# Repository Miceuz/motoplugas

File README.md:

motoplugas
==========

A revolution counting jig for variable frequency drive driven pulley system

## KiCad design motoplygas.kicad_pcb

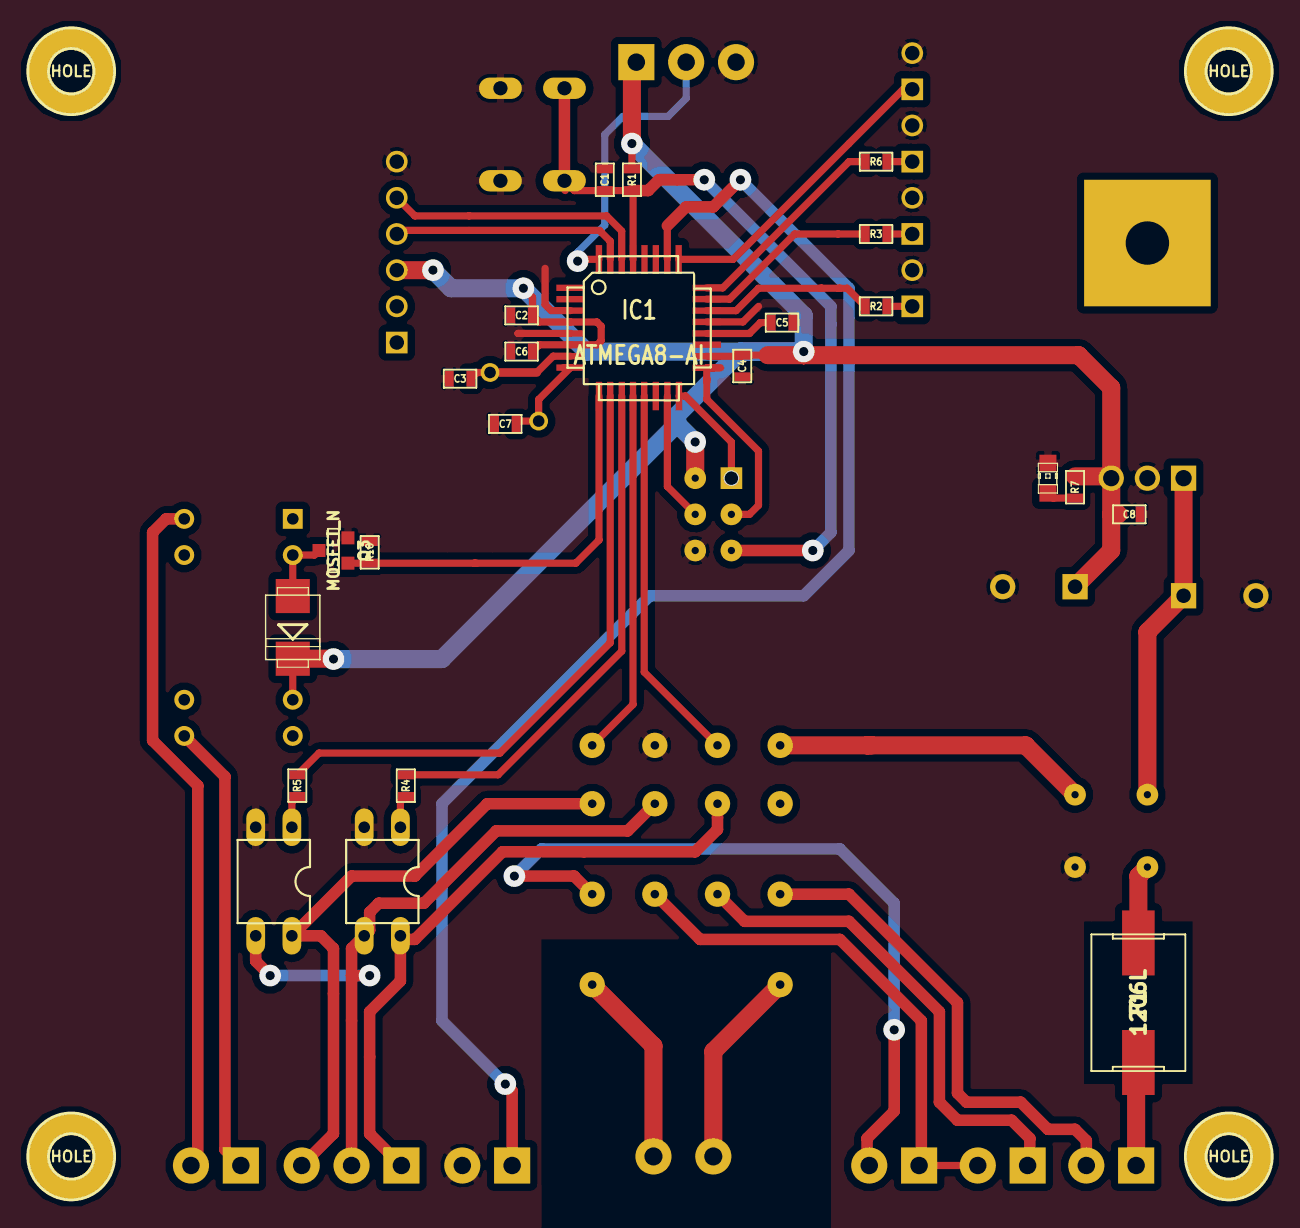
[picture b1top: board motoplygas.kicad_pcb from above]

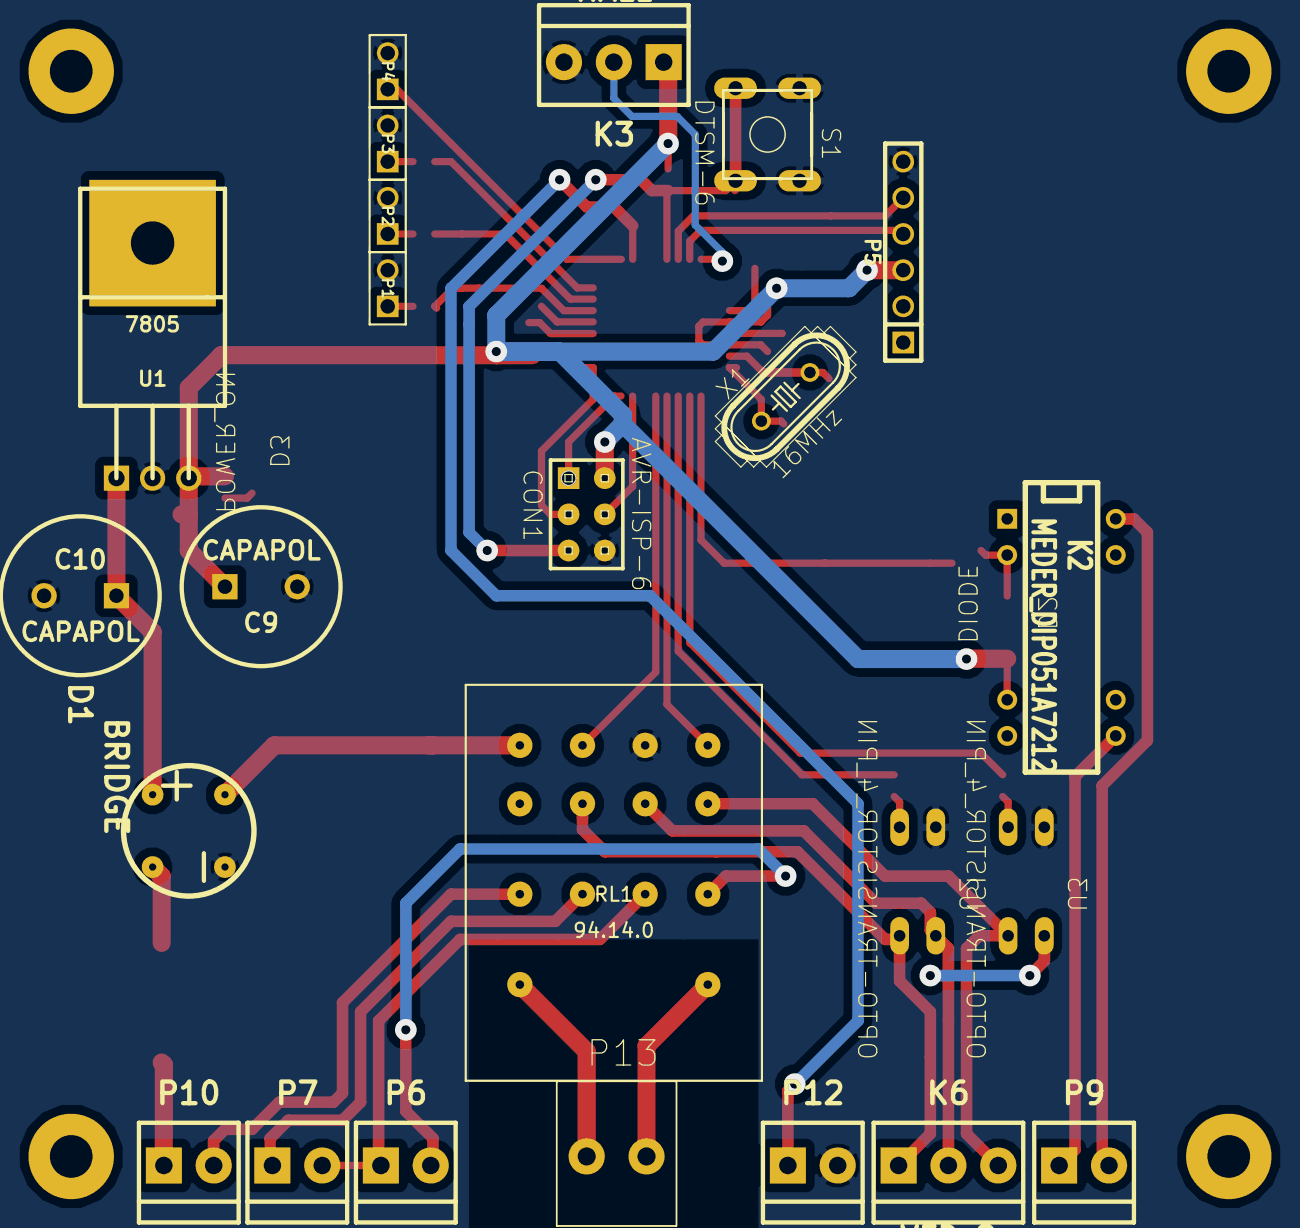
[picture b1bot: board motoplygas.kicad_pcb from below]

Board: 2 copper layers, 49 parts (22 on the bottom side), 44 nets.

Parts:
C1, C2, C4, C5, C6, C8: C; SM0603_Capa
C3, C7: 18pF; SM0603_Capa
C9, C10: CAPAPOL; C2V10
CON1: AVR-ISP-6; atmel-AVR-ISP-6
D1: BRIDGE; Bridge-rond
D2: DIODE; diode-SMB
D3: POWER_ON; led-CHIP-LED0805
F1: 1206L; ptc-littlefuse-3425L
HOLE: Val**; HOLE_30
HOLE#2, HOLE#3, HOLE#4: Val**; HOLE_30
IC1: ATMEGA8-AI; TQFP32
K2: MEDER_DIP051A7212; DIP-14_RELAY
K3: HALL; conn3_35
K6: VFD_2; conn3_35
P1: LED_BOTTOM; PIN_ARRAY_2X1
P2: LED_MIDDLE; PIN_ARRAY_2X1
P3: LED_TOP; PIN_ARRAY_2X1
P4: PROGRAM_BUTTON; PIN_ARRAY_2X1
P5: USB_UART; PIN_ARRAY-6X1
P6: up_button; conn35
P7: down_button; conn35
P9: VFD_1; conn35
P10: 12AC; conn35
P12: MCU_MODE; conn35
P13: RLY_ON; connect-CLAMP-02
Q3: MOSFET_N; SOT23GDS
R1, R2, R3, R4, R5, R6, R10: R; SM0603
R7: 1k; SM0603
RL1: 94.14.0
S1: DTSM-6; switch-tact-DTS-6
U1: 7805; TO220
U2, U3: OPTO-TRANSISTOR_4_PIN; optocoupler-2-DIL04
X1: 16MHz; crystal-HC49/S

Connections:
/+V: K2.8, P9.1
/SC: K6.2, RL1.6, U2.3, U3.3
/analog_input: K2.14, P9.2
/db_bot: P6.1, P7.2, RL1.10
/db_top: P7.1, RL1.11
/digital_input0: K6.1, RL1.7, U2.4
/digital_input1: K6.3, RL1.5, U3.4
/down_button_sense: IC1.13, RL1.3
/down_switch: IC1.10, R5.1
/hall_sensor: IC1.32, K3.2
/mode_programming: IC1.26, P12.1
/reset: C1.1, CON1.5, IC1.29, R1.1, S1.3, S1.4
/rxd: IC1.30, P5.5
/speed_select: IC1.9, Q3.G, R10.1
/txd: IC1.31, P5.4
/ub_top: P6.2, RL1.9
/up_button_sense: IC1.12, RL1.1
/up_switch: IC1.11, R4.1
GND: C1.2, C2.2, C3.1, C4.1, C5.1, C6.1, C7.1, C8.2, C9.2, C10.2, CON1.6, D1.1, D3.2, IC1.3, IC1.5, IC1.21, K3.3, P1.2, P2.2, P3.2, P4.2, P5.6, P12.2, Q3.S, R10.2, RL1.2, S1.1, S1.2, U1.2, U2.2, U3.2
unnamed: P2.1, R3.2
unnamed: P3.1, R6.2
unnamed: D1.4, F1.P$1
unnamed: CON1.4, IC1.15
unnamed: CON1.3, IC1.17
unnamed: CON1.1, IC1.16
unnamed: IC1.25, P4.1
unnamed: IC1.24, R6.1
unnamed: P1.1, R2.2
unnamed: R5.2, U3.1
unnamed: R4.2, U2.1
unnamed: D3.1, R7.1
unnamed: D2.1, K2.2, Q3.D
unnamed: D1.2, RL1.4
unnamed: F1.P$2, P10.1
unnamed: P10.2, RL1.12
unnamed: C7.2, IC1.8, X1.1
unnamed: IC1.22, R2.1
unnamed: IC1.23, R3.1
unnamed: P13.1, RL1.14
unnamed: C10.1, D1.3, U1.1
unnamed: P13.2, RL1.13
unnamed: C5.2, IC1.20
unnamed: C3.2, IC1.7, X1.2
VCC: C2.1, C4.2, C6.2, C8.1, C9.1, CON1.2, D2.2, IC1.4, IC1.6, IC1.18, K2.6, K3.1, P5.3, R1.2, R7.2, U1.3

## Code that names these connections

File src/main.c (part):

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#define MODE_PULL_DOWN PC5

#define HALL_SENSE PD2
#define SPEED_SELECT PD5
#define DOWN_SWITCH PD6
#define UP_SWITCH PD7
#define TRUE 1
#define FALSE 0

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
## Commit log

2013-03-15 initial
2013-03-18 some more changes
2013-04-02 visko daug
2013-04-02 ignore more
2013-04-02 new hex with slow/fast speed set to slow
2013-04-05 some more last changes
2013-10-27 some final changes, don't remember now
